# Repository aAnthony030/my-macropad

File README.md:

# Anthony Pad

This is a custom pad I designed, featuring 8 keys that function as shortcuts and macros, a rotary encoder for volume control, and an OLED display to show the run-time of the macropad.
For this project, I used KiCad to design the PCB, Fusion 360 to model the 3D case, and I wrote the firmware in Python using the KMK library.

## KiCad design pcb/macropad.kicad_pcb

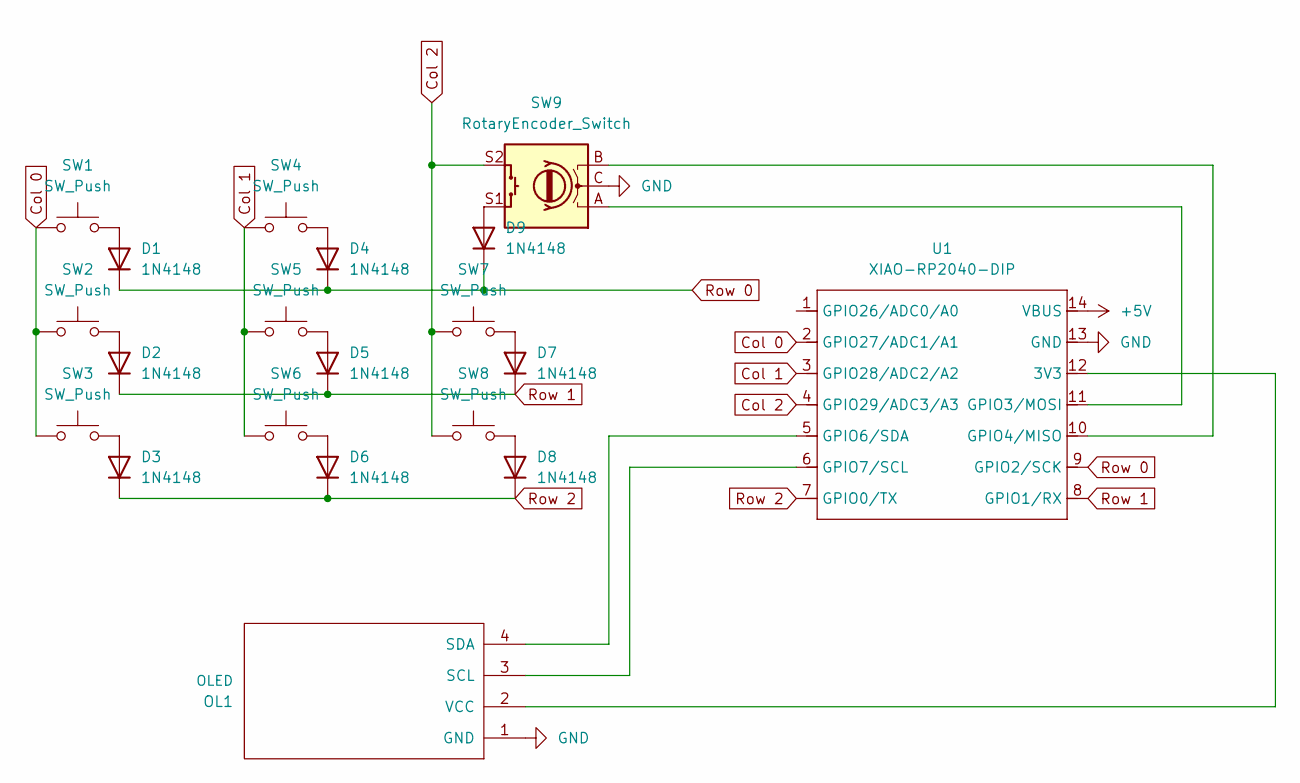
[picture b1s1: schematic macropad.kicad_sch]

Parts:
D1, D2, D3, D4, D5, D6, D7, D8, D9: 1N4148; D_DO-35_SOD27_P7.62mm_Horizontal
OL1: OLED; SSD1306-0.91-OLED-4pin-128x32
SW1, SW2, SW3, SW4, SW5, SW6, SW7, SW8: SW_Push; SW_Cherry_MX_1.00u_PCB
SW9: RotaryEncoder_Switch; RotaryEncoder_Alps_EC11E-Switch_Vertical_H20mm
U1: XIAO-RP2040-DIP

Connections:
+5V: U1.14 (VBUS)
Col 0: SW1.1, SW2.1, SW3.1, U1.2 (GPIO27/ADC1/A1)
Col 1: SW4.1, SW5.1, SW6.1, U1.3 (GPIO28/ADC2/A2)
Col 2: SW7.1, SW8.1, SW9.S2, U1.4 (GPIO29/ADC3/A3)
GND: OL1.1 (GND), SW9.C, U1.13 (GND)
unnamed: D1.2 (A), SW1.2
unnamed: D2.2 (A), SW2.2
unnamed: D3.2 (A), SW3.2
unnamed: D4.2 (A), SW4.2
unnamed: D5.2 (A), SW5.2
unnamed: D6.2 (A), SW6.2
unnamed: D7.2 (A), SW7.2
unnamed: D8.2 (A), SW8.2
unnamed: D9.2 (A), SW9.S1
unnamed: OL1.3 (SCL), U1.6 (GPIO7/SCL)
unnamed: OL1.4 (SDA), U1.5 (GPIO6/SDA)
unnamed: OL1.2 (VCC), U1.12 (3V3)
unnamed: SW9.A, U1.11 (GPIO3/MOSI)
unnamed: SW9.B, U1.10 (GPIO4/MISO)
Row 0: D1.1 (K), D4.1 (K), D9.1 (K), U1.9 (GPIO2/SCK)
Row 1: D2.1 (K), D5.1 (K), D7.1 (K), U1.8 (GPIO1/RX)
Row 2: D3.1 (K), D6.1 (K), D8.1 (K), U1.7 (GPIO0/TX)

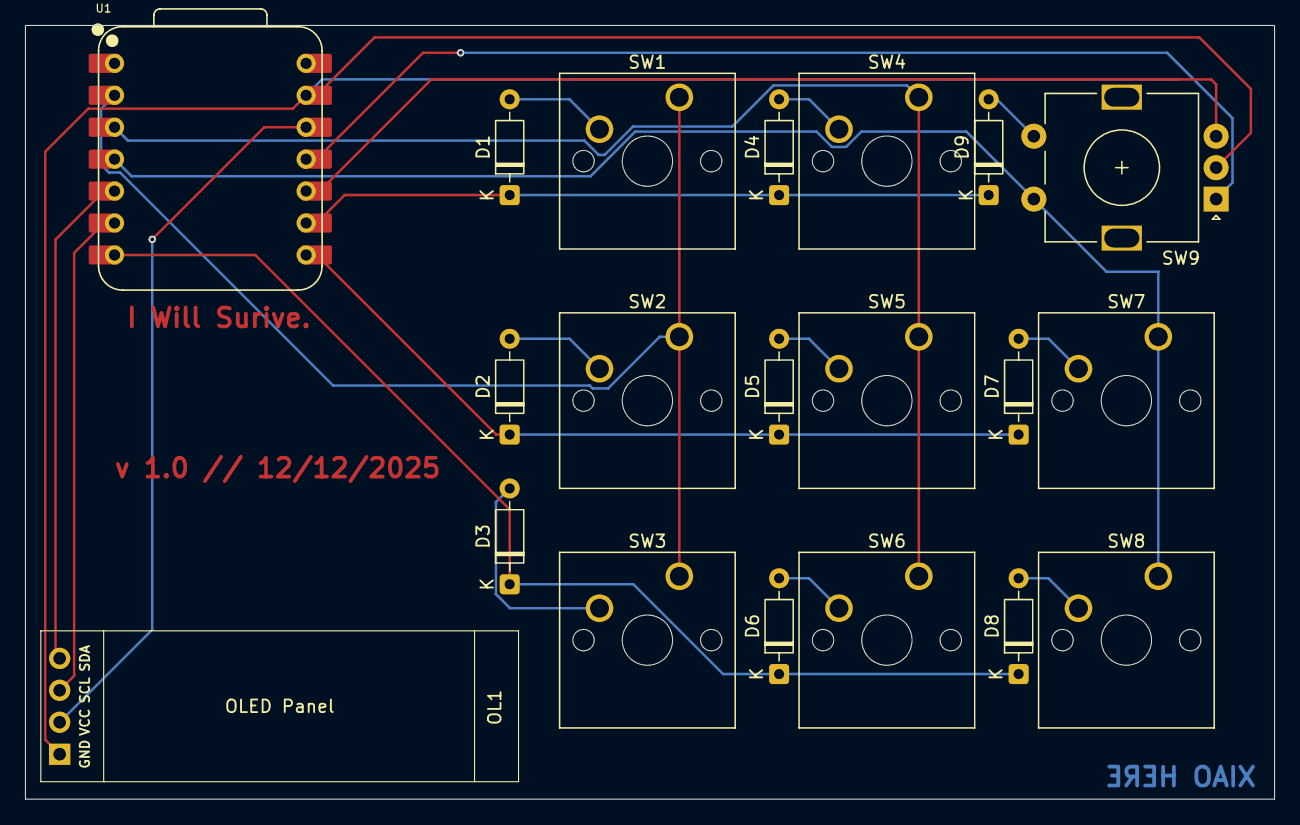
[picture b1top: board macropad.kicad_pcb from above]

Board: 2 copper layers, 99.4 x 61.5 mm, 20 parts (0 on the bottom side), 21 nets.

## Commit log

2025-12-24 added case model
2025-12-24 added bottom_case 3d file
2026-01-11 added stl files
